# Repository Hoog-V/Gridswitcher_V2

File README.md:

# Gridswitcher_V2
MCXN947 based ATS for Solar and Grid

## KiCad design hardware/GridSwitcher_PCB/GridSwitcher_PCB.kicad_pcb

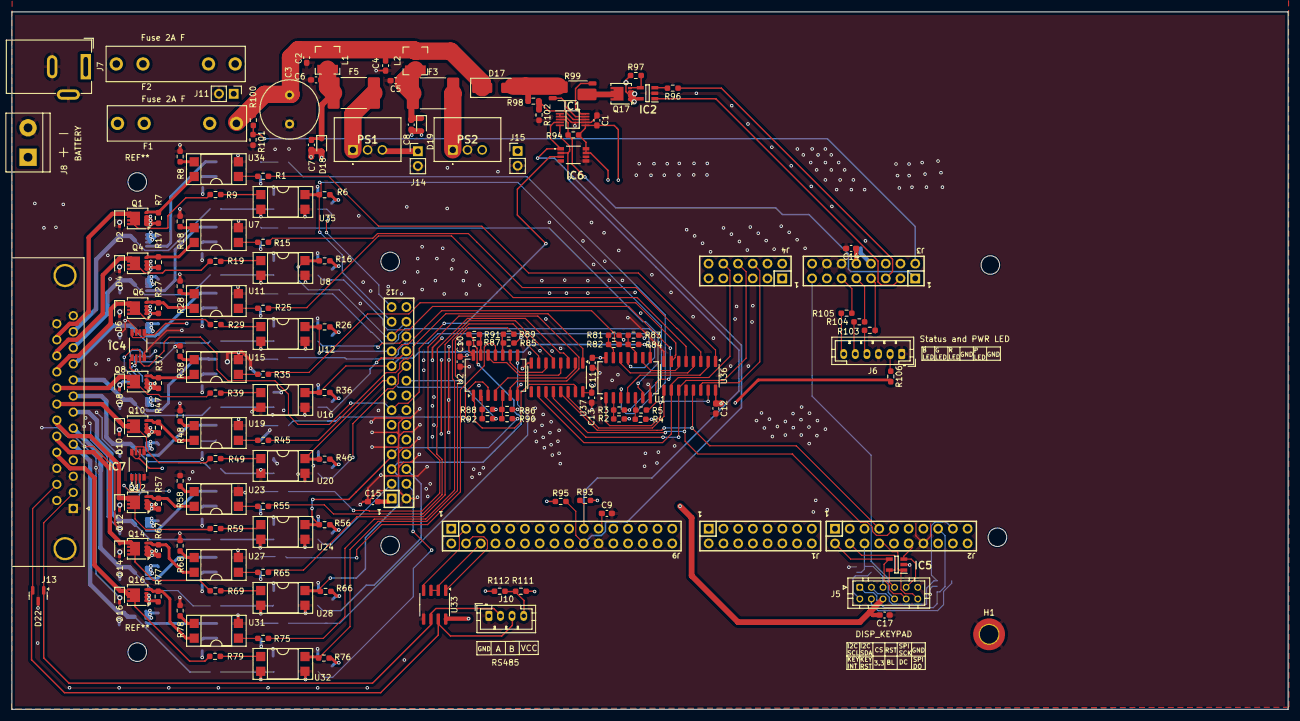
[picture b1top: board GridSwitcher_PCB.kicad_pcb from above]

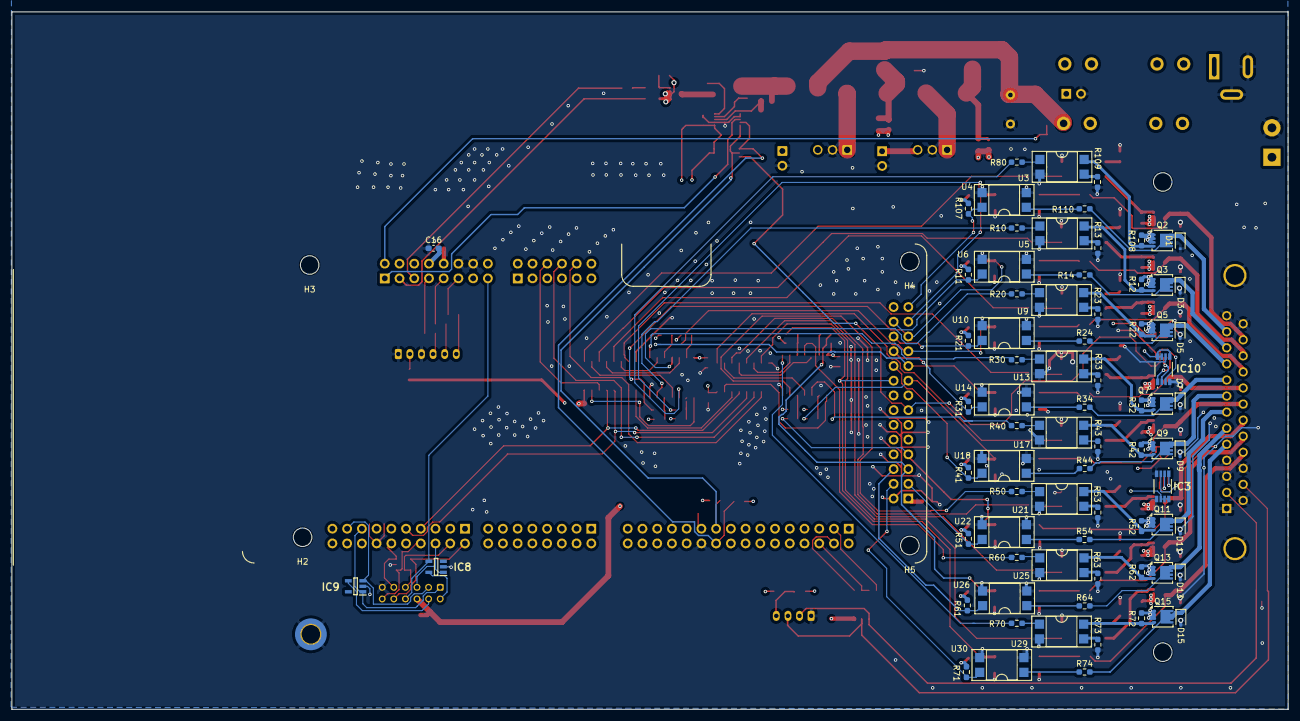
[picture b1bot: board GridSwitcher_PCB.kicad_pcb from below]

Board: 4 copper layers, 220.1 x 120.3 mm, 241 parts (81 on the bottom side), 182 nets.

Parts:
C1, C9, C10, C11, C12, C13, C14, C15, C16, C17: 100n; C_0603_1608Metric_Pad1.08x0.95mm_HandSolder
C2, C4, C5, C6: 10u; C_0603_1608Metric_Pad1.08x0.95mm_HandSolder
C3: 220u; C_Radial_D10.0mm_H12.5mm_P5.00mm
C7, C8: 1n; C_0603_1608Metric_Pad1.08x0.95mm_HandSolder
D1, D2, D3, D4, D5, D6, D7, D8, D9, D10, D11, D12, D13, D14, D15, D16: BAS16J; D_SOD-323F
D17: SS510; D_SMA_Handsoldering
D18, D19: D; D_SOD-323F
D22: SM712_SOT23; SOT-23
F1, F2: GLASS T3; Fuseholder_Littelfuse_100_series_5x20mm
F3, F5: Fuse; Fuse_2920_7451Metric_Pad2.10x5.45mm_HandSolder
H1: M4 Shielding Hole; MountingHole_3.2mm_M3_ISO14580_Pad_TopBottom
H2, H3, H4, H5: MountingHole; MountingHole_3.2mm_M3
IC1: INA237AIDGSR; SOP50P490X110-10N
IC2: UCC27536DBVR; SOT95P280X145-5N
IC3, IC4, IC6, IC7, IC10: P3T1755DPZ
IC5, IC8, IC9: ESDS304DBVR; SOT95P280X145-5N
J1, J3: SSQ-108-03-T-D
J2: SSQ-110-03-T-D
J4: SSQ-106-03-T-D
J5: Display and Keypad; JST_PHD_B12B-PHDSS_2x06_P2.00mm_Vertical
J6: LEDs; JST_PH_B6B-PH-K_1x06_P2.00mm_Vertical
J7: Barrel_Jack_MountingPin; BarrelJack_Wuerth_6941xx301002
J8: Battery; TerminalBlock_bornier-2_P5.08mm
J9: SSQ-116-03-T-D
J10: Temp Sensor RS485; JST_PH_B4B-PH-K_1x04_P2.00mm_Vertical
J11: +24V; PinHeader_1x02_P2.54mm_Vertical
J12: SSQ-114-03-T-D
J13: UT_OUT; DSUB-25_Female_Horizontal_P2.77x2.84mm_EdgePinOffset7.70mm_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
J14: +3.3V; PinHeader_1x02_P2.54mm_Vertical
J15: +5V; PinHeader_1x02_P2.54mm_Vertical
L1, L2: 100u; L_Bourns-SRN4018
PS1: R-78K3.3-0.5; R78K3305
PS2: R-78CK5.0-0.5; R78K3305
Q1, Q2, Q3, Q4, Q5, Q6, Q7, Q8, Q9, Q10, Q11, Q12, Q13, Q14, Q15, Q16, Q17: DMP3013SFV; Diodes_PowerDI3333-8
R1, R8, R10, R13, R15, R18, R20, R23, R25, R28, R30, R33, R35, R38, R40, R43, R45, R48, R50, R53, R55, R58, R60, R63, R65, R68, R70, R73, R75, R78, R80, R103, R104, R105, R106, R109: 1k; R_0603_1608Metric_Pad0.98x0.95mm_HandSolder
R2, R4, R81, R83, R85, R86, R87, R88, R102, R111, R112: DNP; R_0603_1608Metric_Pad0.98x0.95mm_HandSolder
R3, R5, R82, R84, R89, R90, R91, R92, R98: 0; R_0603_1608Metric_Pad0.98x0.95mm_HandSolder
R6, R7, R11, R12, R16, R17, R21, R22, R26, R27, R31, R32, R36, R37, R41, R42, R46, R47, R51, R52, R56, R57, R61, R62, R66, R67, R71, R72, R76, R77, R97, R100, R107, R108: 100k; R_0603_1608Metric_Pad0.98x0.95mm_HandSolder
R9, R14, R19, R24, R29, R34, R39, R44, R49, R54, R59, R64, R69, R74, R79, R96, R110: 4.7k; R_0603_1608Metric_Pad0.98x0.95mm_HandSolder
R93, R94, R95, R101: 10k; R_0603_1608Metric_Pad0.98x0.95mm_HandSolder
R99: R_Shunt; R_Shunt_Vishay_WSK2512_6332Metric_T2.21mm
U1, U2: 74LS09; SO-14_5.3x10.2mm_P1.27mm
U3, U4, U5, U6, U7, U8, U9, U10, U11, U12, U13, U14, U15, U16, U17, U18, U19, U20, U21, U22, U23, U24, U25, U26, U27, U28, U29, U30, U31, U32, U34, U35: PC817; DIP-4_W7.62mm_SMDSocket_SmallPads
U33: SN65HVD11HD; SOIC-8_3.9x4.9mm_P1.27mm
U36, U37: 74HC595; SOIC-16_3.9x9.9mm_P1.27mm

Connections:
+3V3: C1.2, C7.2, C9.1, C10.1, C11.1, C12.1, C13.1, C15.2, C16.2, C17.2, D18.2 (A), IC1.6 (VS), IC3.6 (A1), IC3.7 (A0), IC3.8 (VCC), IC4.5 (A2), IC4.8 (VCC), IC6.7 (A0), IC6.8 (VCC), IC7.6 (A1), IC7.8 (VCC), IC10.5 (A2), IC10.7 (A0), IC10.8 (VCC), J3.4, J3.8, J5.6, J9.21, J12.1, J14.1, PS1.3 (+VOUT), R2.2, R4.2, R6.1, R11.1, R16.1, R21.1, R26.1, R31.1, R36.1, R41.1, R46.1, R51.1, R56.1, R61.1, R66.1, R71.1, R76.1, R81.2, R83.2, R85.2, R86.2, R87.2, R88.2, R93.1, R94.1, R95.1, R106.2, R107.1, R112.2, U1.14 (VCC), U2.14 (VCC), U33.8 (VCC), U36.16 (VCC), U37.16 (VCC)
+5V: C8.2, C14.1, D19.2 (A), J3.10, J15.1, PS2.3 (+VOUT), R111.1
+24V: C2.1, C3.1, C4.1, D17.1 (K), F1.1, J11.1, L1.1, L2.1, Q1.1 (S), Q1.2 (S), Q1.3 (S), Q2.1 (S), Q2.2 (S), Q2.3 (S), Q3.1 (S), Q3.2 (S), Q3.3 (S), Q4.1 (S), Q4.2 (S), Q4.3 (S), Q5.1 (S), Q5.2 (S), Q5.3 (S), Q6.1 (S), Q6.2 (S), Q6.3 (S), Q7.1 (S), Q7.2 (S), Q7.3 (S), Q8.1 (S), Q8.2 (S), Q8.3 (S), Q9.1 (S), Q9.2 (S), Q9.3 (S), Q10.1 (S), Q10.2 (S), Q10.3 (S), Q11.1 (S), Q11.2 (S), Q11.3 (S), Q12.1 (S), Q12.2 (S), Q12.3 (S), Q13.1 (S), Q13.2 (S), Q13.3 (S), Q14.1 (S), Q14.2 (S), Q14.3 (S), Q15.1 (S), Q15.2 (S), Q15.3 (S), Q16.1 (S), Q16.2 (S), Q16.3 (S), R7.1, R12.1, R17.1, R22.1, R27.1, R32.1, R37.1, R42.1, R47.1, R52.1, R57.1, R62.1, R67.1, R72.1, R77.1, R100.1, R108.1
/BAT_CHG_EN: IC2.1 (EN), J3.3
/BAT_CHG_SW: J3.5, R96.1
/DISPLAY_BL: IC8.4 (I/O3), J3.15, J5.8
/DISPLAY_CS: IC8.1 (I/O1), J2.6, J5.5
/DISPLAY_DC: IC5.4 (I/O3), J2.2, J5.10
/DISPLAY_MOSI: IC5.1 (I/O1), J2.8, J5.12
/DISPLAY_RST: IC5.5 (I/O4), J2.4, J5.7
/DISPLAY_SCK: IC5.3 (I/O2), J2.12, J5.9
/I2C_SCL: IC1.5 (SCL), IC3.2 (SCL), IC4.2 (SCL), IC6.2 (SCL), IC7.2 (SCL), IC10.2 (SCL), J9.19, R93.2
/I2C_SCL1: IC9.1 (I/O1), J2.15, J5.1
/I2C_SDA: IC1.4 (SDA), IC3.1 (SDA), IC4.1 (SDA), IC6.1 (SDA), IC7.1 (SDA), IC10.1 (SDA), J9.20, R95.2
/I2C_SDA1: IC9.3 (I/O2), J2.17, J5.3
/KEY_INT: IC8.5 (I/O4), J5.2
/KEY_RST: IC9.4 (I/O3), J5.4
/MCU_MOS_1_IN: U1.1, U36.15 (QA)
/MCU_MOS_3_IN: U1.4, U36.2 (QC)
/MCU_MOS_5_IN: U1.12, U36.4 (QE)
/MCU_MOS_7_IN: U1.9, U36.6 (QG)
/MCU_MOS_9_IN: U2.1, U37.15 (QA)
/MCU_MOS_11_IN: U2.4, U37.2 (QC)
/MCU_MOS_13_IN: U2.12, U37.4 (QE)
/MCU_MOS_15_IN: U2.9, U37.6 (QG)
/MOS_1_IN: R80.1, U1.3
/MOS_1_ON: J12.27, R107.2, U4.4
/MOS_2_IN: R1.1, U36.1 (QB)
/MOS_2_ON: J12.25, R3.1, R6.2, U35.4
/MOS_3_IN: R10.1, U1.6
/MOS_3_ON: J12.26, R11.2, U6.4
/MOS_4_IN: R15.1, U36.3 (QD)
/MOS_4_ON: J12.23, R5.1, R16.2, U8.4
/MOS_5_IN: R20.1, U1.11
/MOS_5_ON: J12.24, R21.2, U10.4
/MOS_6_IN: R25.1, U36.5 (QF)
/MOS_6_ON: J12.21, R26.2, R82.1, U12.4
/MOS_7_IN: R30.1, U1.8
/MOS_7_ON: J12.22, R31.2, U14.4
/MOS_8_IN: R35.1, U36.7 (QH)
/MOS_8_ON: J12.19, R36.2, R84.1, U16.4
/MOS_9_IN: R40.1, U2.3
/MOS_9_ON: J12.20, R41.2, U18.4
/MOS_10_IN: R45.1, U37.1 (QB)
/MOS_10_ON: J12.17, R46.2, R92.1, U20.4
/MOS_11_IN: R50.1, U2.6
/MOS_11_ON: J12.3, R51.2, U22.4
/MOS_12_IN: R55.1, U37.3 (QD)
/MOS_12_ON: J12.7, R56.2, R90.1, U24.4
/MOS_13_IN: R60.1, U2.11
/MOS_13_ON: J12.6, R61.2, U26.4
/MOS_14_IN: R65.1, U37.5 (QF)
/MOS_14_ON: J12.5, R66.2, R91.1, U28.4
/MOS_15_IN: R70.1, U2.8
/MOS_15_ON: J12.4, R71.2, U30.4
/MOS_16_IN: R75.1, U37.7 (QH)
/MOS_16_ON: J12.18, R76.2, R89.1, U32.4
/RS485_A: D22.1 (A1), J10.2, J13.2, U33.6 (A)
/RS485_B: D22.2 (A2), J10.3, J13.15, U33.7 (B)
/RS485_RTS: J9.6, U33.2 (~RE), U33.3 (DE)
/RS485_RXD: J9.4, U33.1 (R)
/RS485_TXD: J9.3, U33.4 (D)
/SHIFT_REG_CLK: J4.8, U36.11 (SRCLK), U37.11 (SRCLK)
/SHIFT_REG_CLR: J4.10, U36.10 (~SRCLR), U37.10 (~SRCLR)
/SHIFT_REG_LAT: J2.9, U36.12 (RCLK), U37.12 (RCLK)
/SHIFT_REG_OE: J2.7, U36.13 (~OE), U37.13 (~OE)
/SHIFT_REG_SER: J4.6, U36.14 (SER)
/SHUNT_AMP_ALERT: IC1.3 (ALERT), J3.1, R94.2
/STATUS_LED_B: J3.11, R105.2
/STATUS_LED_G: J3.9, R104.2
/STATUS_LED_R: J3.7, R103.2
/TEMP_ALERT: IC3.3 (~ALERT), IC4.3 (~ALERT), IC6.3 (~ALERT), IC7.3 (~ALERT), IC10.3 (~ALERT), J12.13
/VOLT_MEAS_BATT: J3.2, R100.2, R101.1
/mosfet_drivers/MOS_1_OUT: D1.1 (K), J13.12, Q2.5 (D), R110.2
/mosfet_drivers/MOS_2_OUT: D2.1 (K), J13.24, Q1.5 (D), R9.2
/mosfet_drivers/MOS_3_OUT: D3.1 (K), J13.11, Q3.5 (D), R14.2
/mosfet_drivers/MOS_4_OUT: D4.1 (K), J13.23, Q4.5 (D), R19.2
/mosfet_drivers/MOS_5_OUT: D5.1 (K), J13.10, Q5.5 (D), R24.2
/mosfet_drivers/MOS_6_OUT: D6.1 (K), J13.22, Q6.5 (D), R29.2
/mosfet_drivers/MOS_7_OUT: D7.1 (K), J13.9, Q7.5 (D), R34.2
/mosfet_drivers/MOS_8_OUT: D8.1 (K), J13.21, Q8.5 (D), R39.2
/mosfet_drivers/MOS_9_OUT: D9.1 (K), J13.8, Q9.5 (D), R44.2
/mosfet_drivers/MOS_10_OUT: D10.1 (K), J13.20, Q10.5 (D), R49.2
/mosfet_drivers/MOS_11_OUT: D11.1 (K), J13.7, Q11.5 (D), R54.2
/mosfet_drivers/MOS_12_OUT: D12.1 (K), J13.19, Q12.5 (D), R59.2
/mosfet_drivers/MOS_13_OUT: D13.1 (K), J13.6, Q13.5 (D), R64.2
/mosfet_drivers/MOS_14_OUT: D14.1 (K), J13.18, Q14.5 (D), R69.2
/mosfet_drivers/MOS_15_OUT: D15.1 (K), J13.5, Q15.5 (D), R74.2
/mosfet_drivers/MOS_16_OUT: D16.1 (K), J13.17, Q16.5 (D), R79.2
GND: C1.1, C2.2, C3.2, C4.2, C5.2, C6.2, C9.2, C10.2, C11.2, C12.2, C13.2, C14.2, C15.1, C16.1, C17.1, D1.2 (A), D2.2 (A), D3.2 (A), D4.2 (A), D5.2 (A), D6.2 (A), D7.2 (A), D8.2 (A), D9.2 (A), D10.2 (A), D11.2 (A), D12.2 (A), D13.2 (A), D14.2 (A), D15.2 (A), D16.2 (A), D22.3 (common), H1.1, IC1.1 (A1), IC1.2 (A0), IC1.7 (GND), IC2.2 (GND), IC3.4 (GND), IC3.5 (A2), IC4.4 (GND), IC4.6 (A1), IC4.7 (A0), IC5.2 (GND), IC6.4 (GND), IC6.5 (A2), IC6.6 (A1), IC7.4 (GND), IC7.5 (A2), IC7.7 (A0), IC8.2 (GND), IC9.2 (GND), IC10.4 (GND), IC10.6 (A1), J2.14, J3.12, J3.14, J5.11, J6.1, J6.3, J7.2, J7.3 (MountPin), J8.2, J9.22, J10.1, J11.2, J12.2, J13.0 (PAD), J13.1, J13.3, J13.4, J13.13, J13.14, J13.16, J13.25, J14.2, J15.2, PS1.2 (GND), PS2.2 (GND), R8.2, R13.2, R18.2, R23.2, R28.2, R33.2, R38.2, R43.2, R48.2, R53.2, R58.2, R63.2, R68.2, R73.2, R78.2, R101.2, R102.2, R109.2, U1.7 (GND), U2.7 (GND), U3.2, U4.2, U4.3, U5.2, U6.2, U6.3, U7.2, U8.2, U8.3, U9.2, U10.2, U10.3, U11.2, U12.2, U12.3, U13.2, U14.2, U14.3, U15.2, U16.2, U16.3, U17.2, U18.2, U18.3, U19.2, U20.2, U20.3, U21.2, U22.2, U22.3, U23.2, U24.2, U24.3, U25.2, U26.2, U26.3, U27.2, U28.2, U28.3, U29.2, U30.2, U30.3, U31.2, U32.2, U32.3, U33.5 (GND), U34.2, U35.2, U35.3, U36.8 (GND), U37.8 (GND)
unnamed: D17.2 (A), R98.2, R99.4
unnamed: C6.1, C7.1, D18.1 (K), F5.1, L1.2
unnamed: C5.1, C8.1, D19.1 (K), F3.1, L2.2
unnamed: F2.2, J7.1
unnamed: IC1.10 (IN+), R99.2
unnamed: IC1.9 (IN-), R99.3
unnamed: IC1.8 (VBUS), R98.1, R102.1
unnamed: IC2.3 (IN-), R96.2
unnamed: IC2.4 (OUT), Q17.4 (G), R97.2
unnamed: F2.1, IC2.5 (VDD), Q17.1 (S), Q17.2 (S), Q17.3 (S), R97.1
unnamed: J6.2, R106.1
unnamed: J6.4, R103.1
unnamed: J6.5, R104.1
unnamed: J6.6, R105.1
unnamed: F1.2, J8.1
unnamed: J10.4, R111.2, R112.1
unnamed: F5.2, PS1.1 (+VIN)
unnamed: F3.2, PS2.1 (+VIN)
unnamed: Q1.4 (G), R7.2, U34.4
unnamed: Q2.4 (G), R108.2, U3.4
unnamed: Q3.4 (G), R12.2, U5.4
unnamed: Q4.4 (G), R17.2, U7.4
unnamed: Q5.4 (G), R22.2, U9.4
unnamed: Q6.4 (G), R27.2, U11.4
unnamed: Q7.4 (G), R32.2, U13.4
unnamed: Q8.4 (G), R37.2, U15.4
unnamed: Q9.4 (G), R42.2, U17.4
unnamed: Q10.4 (G), R47.2, U19.4
unnamed: Q11.4 (G), R52.2, U21.4
unnamed: Q12.4 (G), R57.2, U23.4
unnamed: Q13.4 (G), R62.2, U25.4
unnamed: Q14.4 (G), R67.2, U27.4
unnamed: Q15.4 (G), R72.2, U29.4
unnamed: Q16.4 (G), R77.2, U31.4
unnamed: Q17.5 (D), R99.1
unnamed: R1.2, U34.1
unnamed: R2.1, R3.2, U1.2
unnamed: R4.1, R5.2, U1.5
unnamed: R8.1, U34.3
unnamed: R9.1, U35.1
unnamed: R10.2, U5.1
unnamed: R13.1, U5.3
unnamed: R14.1, U6.1
unnamed: R15.2, U7.1
unnamed: R18.1, U7.3
unnamed: R19.1, U8.1
unnamed: R20.2, U9.1
unnamed: R23.1, U9.3
unnamed: R24.1, U10.1
unnamed: R25.2, U11.1
unnamed: R28.1, U11.3
unnamed: R29.1, U12.1
unnamed: R30.2, U13.1
unnamed: R33.1, U13.3
unnamed: R34.1, U14.1
unnamed: R35.2, U15.1
unnamed: R38.1, U15.3
unnamed: R39.1, U16.1
unnamed: R40.2, U17.1
unnamed: R43.1, U17.3
unnamed: R44.1, U18.1
unnamed: R45.2, U19.1
unnamed: R48.1, U19.3
unnamed: R49.1, U20.1
unnamed: R50.2, U21.1
unnamed: R53.1, U21.3
unnamed: R54.1, U22.1
unnamed: R55.2, U23.1
unnamed: R58.1, U23.3
unnamed: R59.1, U24.1
unnamed: R60.2, U25.1
unnamed: R63.1, U25.3
unnamed: R64.1, U26.1
unnamed: R65.2, U27.1
unnamed: R68.1, U27.3
unnamed: R69.1, U28.1
unnamed: R70.2, U29.1
unnamed: R73.1, U29.3
unnamed: R74.1, U30.1
unnamed: R75.2, U31.1
unnamed: R78.1, U31.3
unnamed: R79.1, U32.1
unnamed: R80.2, U3.1
unnamed: R81.1, R82.2, U1.13
unnamed: R83.1, R84.2, U1.10
unnamed: R85.1, R89.2, U2.10
unnamed: R86.1, R90.2, U2.5
unnamed: R87.1, R91.2, U2.13
unnamed: R88.1, R92.2, U2.2
unnamed: R109.1, U3.3
unnamed: R110.1, U4.1
unnamed: U36.9 (QH'), U37.14 (SER)

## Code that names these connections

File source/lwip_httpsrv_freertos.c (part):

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#define ILI9488_RST     10 // P0_10
#define ILI9488_USE_RST 1

#define I2C_SCL  2 //P3_2
#define I2C_SDA 3 //P3_3

#define I2C_SCL1 1 //P1_1
#define I2C_SDA1 0 //P1_0

#define UART1_RXD 16 //P1_16
#define UART1_TXD 17 //P1_17
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    LP_FLEXCOMM_Init(3, LP_FLEXCOMM_PERIPH_LPI2C);
     CLOCK_SetClkDiv(kCLOCK_DivFlexcom3Clk, 1u);
     CLOCK_AttachClk(kFRO12M_to_FLEXCOMM3);
    //  PORT_SetPinMux(PORT1, I2C_SCL1, kPORT_MuxAlt2);
    //  PORT_SetPinMux(PORT1, I2C_SDA1, kPORT_MuxAlt2);
    port_pin_config_t port_cfg = {.driveStrength = kPORT_LowDriveStrength, 
                                  .inputBuffer = kPORT_InputBufferEnable, 
                                  .invertInput = kPORT_InputNormal, 
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                                  .pullSelect=kPORT_PullDisable, 
                                  .pullValueSelect=0, 
                                  .slewRate=kPORT_FastSlewRate};
     PORT_SetPinConfig(PORT1, I2C_SCL1, &port_cfg);
     PORT_SetPinConfig(PORT1, I2C_SDA1, &port_cfg);

     vTaskDelay(100/portTICK_PERIOD_MS);
     LPI2C_MasterGetDefaultConfig(&ads_config);
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     }
}

#define SHUNT_AMP_ALERT_PIN 0 // P2_0
#define SHUNT_AMP_ALERT_PORT PORT2
#define TEMP_ALERT_PIN 8 // P2_8
#define TEMP_ALERT_PORT PORT2
#define BAT_CHG_EN_PIN 22 // P1_22
#define BAT_CHG_EN_PORT PORT1
#define MOS_1_IN_PIN 0 // P4_0
#define MOS_1_IN_PORT PORT4
#define MOS_2_IN_PIN 1 // P4_1
#define MOS_2_IN_PORT PORT4
#define MOS_3_IN_PIN 5 // P4_5
#define MOS_3_IN_PORT PORT4
#define MOS_4_IN_PIN 6 // P4_6
#define MOS_4_IN_PORT PORT4
#define MOS_5_IN_PIN 7 // P4_7
#define MOS_5_IN_PORT PORT4
#define MOS_6_IN_PIN 12 // P4_12
#define MOS_6_IN_PORT PORT4
#define MOS_7_IN_PIN 13 // P4_13
#define MOS_7_IN_PORT PORT4
#define MOS_8_IN_PIN 14 // P4_14
#define MOS_8_IN_PORT PORT4
#define MOS_9_IN_PIN 15 // P4_15
#define MOS_9_IN_PORT PORT4
#define MOS_10_IN_PIN 16 // P4_16
#define MOS_10_IN_PORT PORT4
#define MOS_11_IN_PIN 17 // P4_17
#define MOS_11_IN_PORT PORT4
#define MOS_12_IN_PIN 18 // P4_18
#define MOS_12_IN_PORT PORT4
#define MOS_13_IN_PIN 19 // P4_19
#define MOS_13_IN_PORT PORT4
#define MOS_14_IN_PIN 20 // P4_20
#define MOS_14_IN_PORT PORT4
#define MOS_15_IN_PIN 21 // P4_21
#define MOS_15_IN_PORT PORT4
#define MOS_16_IN_PIN 22 // P4_22
#define MOS_16_IN_PORT PORT4

static void gpio_input_test_task(void *arg) {
     CLOCK_EnableClock(kCLOCK_Port1);
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                                  .pullSelect=kPORT_PullUp, 
                                  .pullValueSelect=1, 
                                  .slewRate=kPORT_FastSlewRate};
     PORT_SetPinConfig(SHUNT_AMP_ALERT_PORT, SHUNT_AMP_ALERT_PIN, &port_cfg);
     PORT_SetPinConfig(PORT2, TEMP_ALERT_PIN, &port_cfg);
     PORT_SetPinConfig(PORT1, BAT_CHG_EN_PIN, &port_cfg);
     PORT_SetPinConfig(PORT4, MOS_1_IN_PIN, &port_cfg);
     PORT_SetPinConfig(PORT4, MOS_2_IN_PIN, &port_cfg);
     PORT_SetPinConfig(PORT4, MOS_3_IN_PIN, &port_cfg);
     PORT_SetPinConfig(PORT4, MOS_4_IN_PIN, &port_cfg);
     PORT_SetPinConfig(PORT4, MOS_5_IN_PIN, &port_cfg);
     for(uint8_t i = 12; i < 23; i++) {
        PORT_SetPinConfig(PORT4, i, &port_cfg);
     }
     uint8_t mosf_in_vals[16];
    while(1) {
        uint8_t shunt_amp_alert_val = GPIO_PinRead(GPIO2, SHUNT_AMP_ALERT_PIN);
        uint8_t temp_alert_val = GPIO_PinRead(GPIO2, TEMP_ALERT_PIN);
        uint8_t bat_chg_en_val = GPIO_PinRead(GPIO1, BAT_CHG_EN_PIN);
        uint32_t port_4_val = GPIO4->PDIR;
        mosf_in_vals[0] = port_4_val & 1;
        mosf_in_vals[1] = (port_4_val >> MOS_2_IN_PIN) & 1;
        mosf_in_vals[2] = (port_4_val >> MOS_3_IN_PIN) & 1;
        mosf_in_vals[3] = (port_4_val >> MOS_4_IN_PIN) & 1;
        mosf_in_vals[4] = (port_4_val >> MOS_5_IN_PIN) & 1;
        for(uint8_t i = 12; i < 23; i++) {
            mosf_in_vals[i-7] = (port_4_val >> i) & 1;
        }
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     LP_FLEXCOMM_Init(5, LP_FLEXCOMM_PERIPH_LPUART);
     CLOCK_SetClkDiv(kCLOCK_DivFlexcom5Clk, 1u);
     CLOCK_AttachClk(kFRO12M_to_FLEXCOMM5);
    //  PORT_SetPinMux(PORT1, I2C_SCL1, kPORT_MuxAlt2);
    //  PORT_SetPinMux(PORT1, I2C_SDA1, kPORT_MuxAlt2);
    port_pin_config_t port_cfg = {.driveStrength = kPORT_LowDriveStrength, 
                                  .inputBuffer = kPORT_InputBufferEnable, 
                                  .invertInput = kPORT_InputNormal, 
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
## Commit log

2024-07-23 -add project_skeleton
2024-07-23 -add cmake and ozone
2024-07-26 -add first rev of schematic
2024-08-03 -enh made some progress on pcb/fp design
2024-08-07 -add some changes to schematic, tested the interfaces (uart, spi and i2c) with some test code
2024-08-08 -add some more pinning changes, add rts flow control for rs485
2024-10-24 -enh final revision; ordered

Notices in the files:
source/lwip_httpsrv_freertos.c:
Copyright (c) 2016, Freescale Semiconductor, Inc.
Copyright 2016-2024 NXP
All rights reserved.
SPDX-License-Identifier: BSD-3-Clause
